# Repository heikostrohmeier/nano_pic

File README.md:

# nano_pic
32-Bit PIC development board in the size and footprint of an arduino nano

it is NOT 1:1 pin compatible to the arduino nano!

I used the Microchip PIC32MX250F128D MCU

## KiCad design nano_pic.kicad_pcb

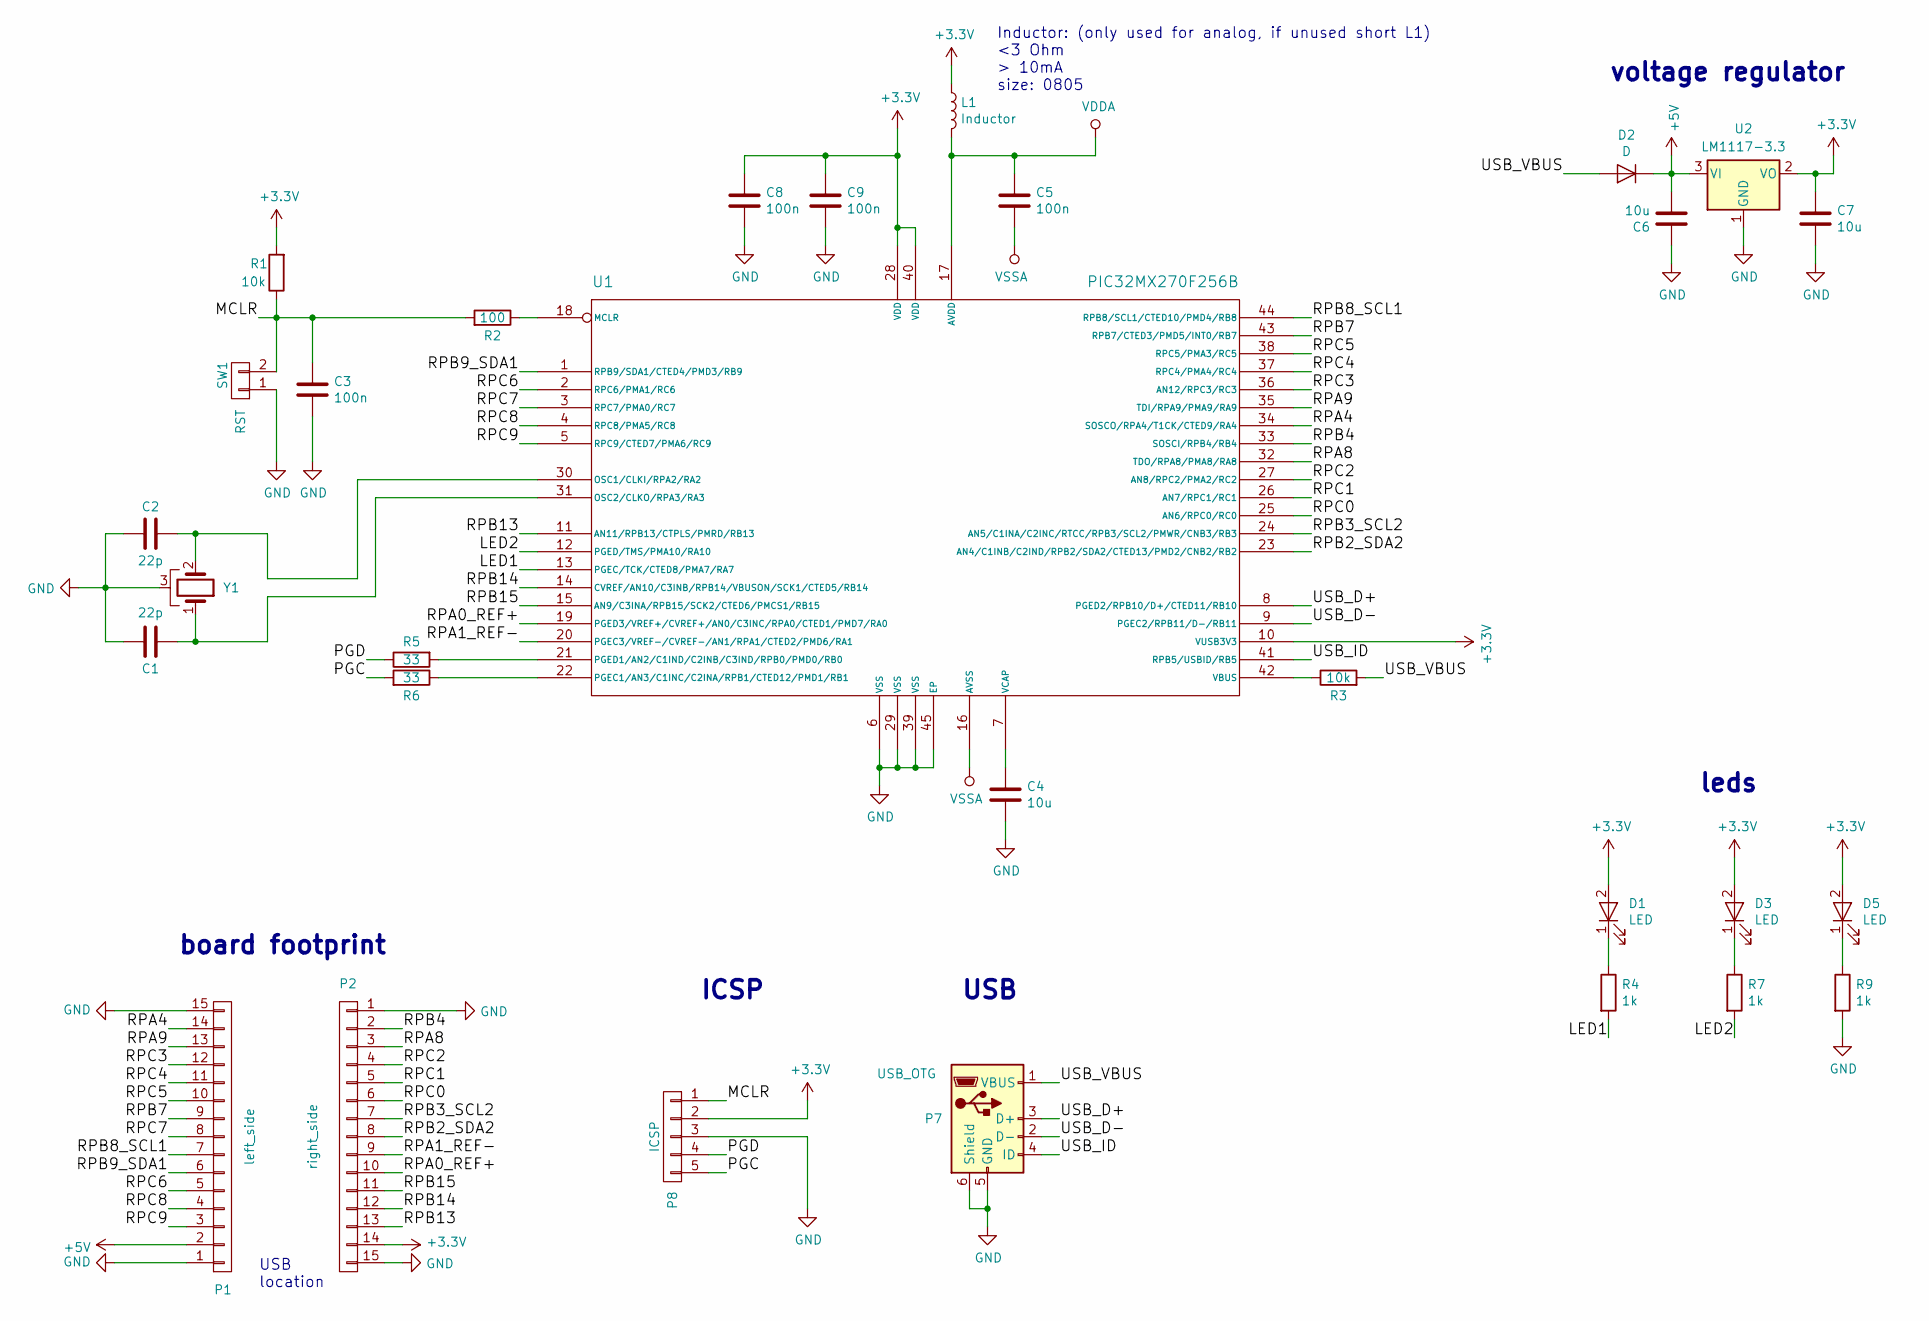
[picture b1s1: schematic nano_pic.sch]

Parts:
C1, C2: 22p; C_0603
C3, C5, C8, C9: 100n; C_0603
C4, C6, C7: 10u; C_0603
D1, D3, D5: LED; LED_0603
D2: D; SOD-123
L1: Inductor; R_0805
P1: left_side; nano_pic_header
P2: right_side; nano_pic_header
P7: USB_OTG; USB_Mini-B_handsolder
P8: ICSP; ICSP_2.54
R1, R3: 10k; R_0603
R2: 100; R_0603
R4, R7, R9: 1k; R_0603
R5, R6: 33; R_0603
SW1: RST; SW_SMD_3x6x2.5mm
U1: PIC32MX270F256B; QFN-44-1EP_8x8mm_Pitch0.65mm
U2: LM1117-3.3; SOT-223-3Lead_TabPin2
Y1: CRYSTAL_SMD; crystal_3225

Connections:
+3V3: C7.1, C8.1, C9.1, D1.2 (A), D3.2 (A), D5.2 (A), L1.1, P2.14, P8.2, R1.2, U1.10 (VUSB3V3), U1.28 (VDD), U1.40 (VDD), U2.2 (VO)
+5V: C6.2, D2.1 (K), P1.2, U2.3 (VI)
/LED1: R4.2, U1.13 (PGEC/TCK/CTED8/PMA7/RA7)
/LED2: R7.2, U1.12 (PGED/TMS/PMA10/RA10)
/MCLR: C3.1, P8.1, R1.1, R2.2, SW1.2
/PGC: P8.5, R6.2
/PGD: P8.4, R5.1
/RPA0_REF+: P2.10, U1.19 (PGED3/VREF+/CVREF+/AN0/C3INC/RPA0/CTED1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)
/RPA1_REF-: P2.9, U1.20 (PGEC3/VREF-/CVREF-/AN1/RPA1/CTED2/PMD6/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)
/RPA4: P1.14, U1.34 (SOSCO/RPA4/T1CK/CTED9/RA4)
/RPA8: P2.3, U1.32 (TDO/RPA8/PMA8/RA8)
/RPA9: P1.13, U1.35 (TDI/RPA9/PMA9/RA9)
/RPB2_SDA2: P2.8, U1.23 (AN4/C1INB/C2IND/RPB2/SDA2/CTED13/PMD2/C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)
/RPB3_SCL2: P2.7, U1.24 (AN5/C1INA/C2INC/RTCC/RPB3/SCL2/PMWR/CNB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)
/RPB4: P2.2, U1.33 (SOSCI/RPB4/RB4)
/RPB7: P1.9, U1.43 (RPB7/CTED3/PMD5/INT0/RB7)
/RPB8_SCL1: P1.7, U1.44 (RPB8/SCL1/CTED10/PMD4/RB8)
/RPB9_SDA1: P1.6, U1.1 (RPB9/SDA1/CTED4/PMD3/RB9)
/RPB13: P2.13, U1.11 (AN11/RPB13/CTPLS/PMRD/RB13)
/RPB14: P2.12, U1.14 (CVREF/AN10/C3INB/RPB14/VBUSON/SCK1/CTED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)
/RPB15: P2.11, U1.15 (AN9/C3INA/RPB15/SCK2/CTED6/PMCS1/RB15)
/RPC0: P2.6, U1.25 (AN6/RPC0/RC0)
/RPC1: P2.5, U1.26 (AN7/RPC1/RC1)
/RPC2: P2.4, U1.27 (AN8/RPC2/PMA2/RC2)
/RPC3: P1.12, U1.36 (AN12/RPC3/RC3)
/RPC4: P1.11, U1.37 (RPC4/PMA4/RC4)
/RPC5: P1.10, U1.38 (RPC5/PMA3/RC5)
/RPC6: P1.5, U1.2 (RPC6/PMA1/RC6)
/RPC7: P1.8, U1.3 (RPC7/PMA0/RC7)
/RPC8: P1.4, U1.4 (RPC8/PMA5/RC8)
/RPC9: P1.3, U1.5 (RPC9/CTED7/PMA6/RC9)
/USB_D+: P7.3 (D+), U1.8 (PGED2/RPB10/D+/CTED11/RB10)
/USB_D-: P7.2 (D-), U1.9 (PGEC2/RPB11/D-/RB11)
/USB_ID: P7.4 (ID), U1.41 (RPB5/USBID/RB5)
/USB_VBUS: D2.2 (A), P7.1 (VBUS), R3.2
GND: C1.2, C2.1, C3.2, C4.2, C6.1, C7.2, C8.2, C9.2, P1.1, P1.15, P2.1, P2.15, P7.5 (GND), P7.6 (Shield), P8.3, R9.2, SW1.1, U1.6 (VSS), U1.29 (VSS), U1.39 (VSS), U1.45 (EP), U2.1 (GND), Y1.3
unnamed: C1.1, U1.31 (OSC2/CLKO/RPA3/RA3), Y1.1
unnamed: C2.2, U1.30 (OSC1/CLKI/RPA2/RA2), Y1.2
unnamed: C4.1, U1.7 (VCAP)
unnamed: D1.1 (K), R4.1
unnamed: D3.1 (K), R7.1
unnamed: D5.1 (K), R9.1
unnamed: R2.1, U1.18 (MCLR)
unnamed: R3.1, U1.42 (VBUS)
unnamed: R5.2, U1.21 (PGED1/AN2/C1IND/C2INB/C3IND/RPB0/PMD0/R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)
unnamed: R6.1, U1.22 (PGEC1/AN3/C1INC/C2INA/RPB1/CTED12/PMD1/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)
VDDA: C5.1, L1.2, U1.17 (AVDD)
VSSA: C5.2, U1.16 (AVSS)

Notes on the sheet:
USB location
Inductor: (only used for analog, if unused short L1) <3 Ohm > 10mA size: 0805
board footprint
leds
ICSP
voltage regulator
USB

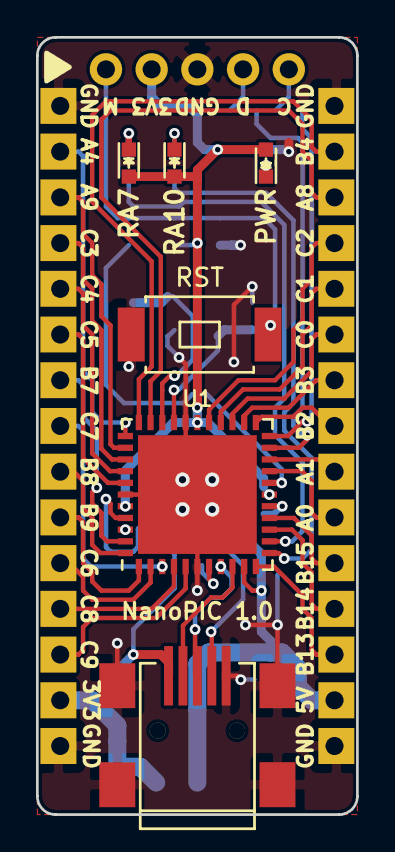
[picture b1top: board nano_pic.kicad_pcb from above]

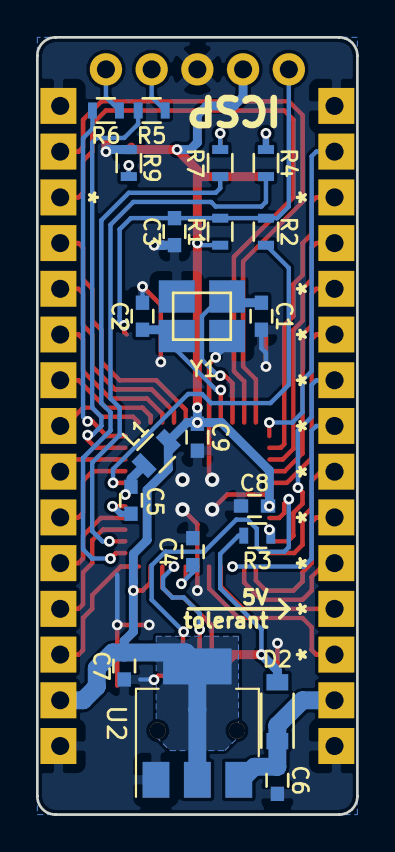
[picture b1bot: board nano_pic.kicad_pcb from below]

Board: 2 copper layers, 17.8 x 43.2 mm, 30 parts (23 on the bottom side), 48 nets.

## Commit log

2017-07-02 kicad files
